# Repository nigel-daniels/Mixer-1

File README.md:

# Mixer

This design is based on the mixer by [Humberto Martínez Barberá](https://www.hackster.io/mb_humberto/eurorack-4-channel-mixer-with-vu-meter-535570). In this design I dropped the peak detection option and added an input channel as I have five VCOs that can generate source signals. I also swapped the electrolytic caps to tantalum as that's what I had on hand.

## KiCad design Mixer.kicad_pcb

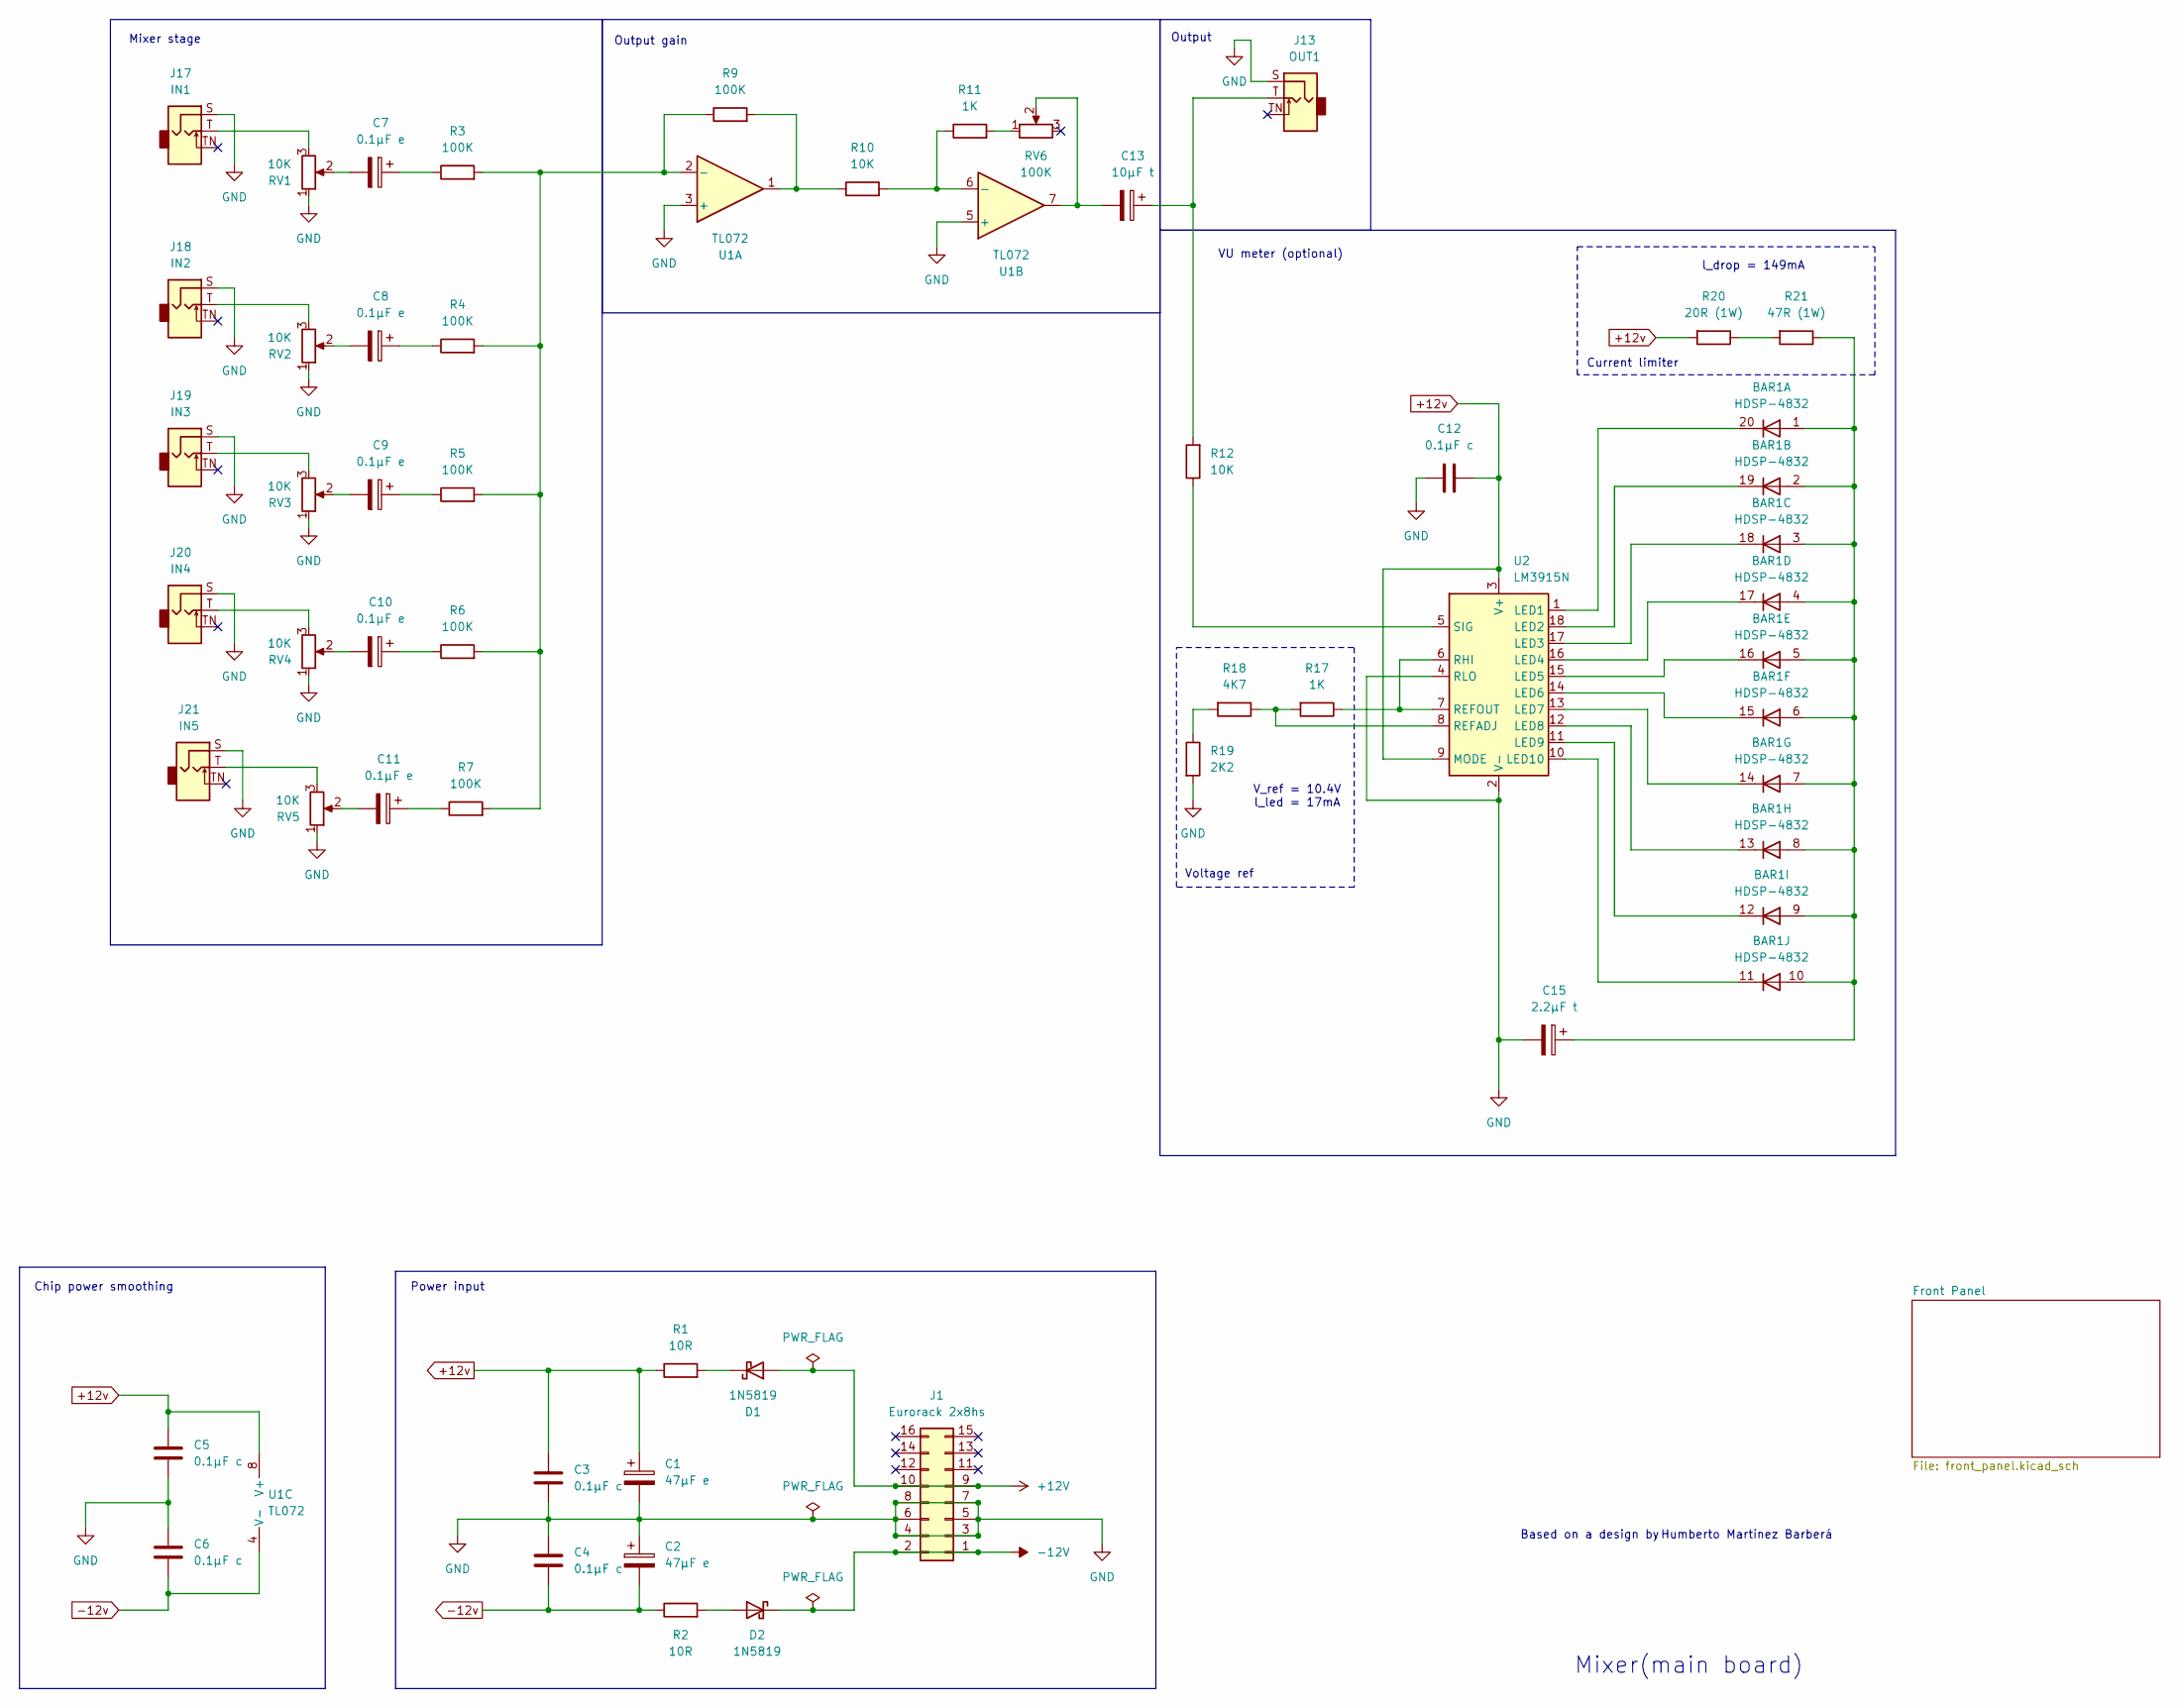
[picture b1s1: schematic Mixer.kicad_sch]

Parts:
BAR1: HDSP-4832
C1, C2: 47μF e; CP_Radial_D5.0mm_P2.50mm
C3, C4, C5, C6, C12: 0.1μF c; C_Disc_D4.7mm_W2.5mm_P5.00mm
C7, C8, C9, C10, C11: 0.1μF e; CP_Radial_D4.0mm_P1.50mm
C13: 10μF t; C_Disc_D4.7mm_W2.5mm_P5.00mm
C15: 2.2μF t; C_Disc_D4.7mm_W2.5mm_P5.00mm
D1, D2: 1N5819; D_DO-41_SOD81_P10.16mm_Horizontal
J1: Eurorack 2x8hs; PinHeader_2x08_P2.54mm_Vertical
J13: OUT1; Jack_3.5mm_QingPu_WQP-PJ398SM_Vertical_CircularHoles
J17: IN1; Jack_3.5mm_QingPu_WQP-PJ398SM_Vertical_CircularHoles
J18: IN2; Jack_3.5mm_QingPu_WQP-PJ398SM_Vertical_CircularHoles
J19: IN3; Jack_3.5mm_QingPu_WQP-PJ398SM_Vertical_CircularHoles
J20: IN4; Jack_3.5mm_QingPu_WQP-PJ398SM_Vertical_CircularHoles
J21: IN5; Jack_3.5mm_QingPu_WQP-PJ398SM_Vertical_CircularHoles
R1, R2: 10R; R_Axial_DIN0204_L3.6mm_D1.6mm_P2.54mm_Vertical
R3, R4, R5, R6, R7: 100K; R_Axial_DIN0204_L3.6mm_D1.6mm_P5.08mm_Horizontal
R9: 100K; R_Axial_DIN0204_L3.6mm_D1.6mm_P2.54mm_Vertical
R10, R12: 10K; R_Axial_DIN0204_L3.6mm_D1.6mm_P5.08mm_Horizontal
R11: 1K; R_Axial_DIN0204_L3.6mm_D1.6mm_P5.08mm_Horizontal
R17: 1K; R_Axial_DIN0204_L3.6mm_D1.6mm_P2.54mm_Vertical
R18: 4K7; R_Axial_DIN0204_L3.6mm_D1.6mm_P2.54mm_Vertical
R19: 2K2; R_Axial_DIN0204_L3.6mm_D1.6mm_P2.54mm_Vertical
R20: 20R (1W); R_Axial_DIN0414_L11.9mm_D4.5mm_P15.24mm_Horizontal
R21: 47R (1W); R_Axial_DIN0617_L17.0mm_D6.0mm_P20.32mm_Horizontal
RV1, RV2, RV3, RV4, RV5: 10K; Potentiometer_Alps_RK09L_Single_Vertical
RV6: 100K; Potentiometer_Alps_RK09L_Single_Vertical
U1: TL072; DIP-8_W7.62mm
U2: LM3915N; DIP-18_W7.62mm

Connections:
+12V: D1.2 (A), J1.9, J1.10
+12v: C1.1, C3.1, C5.1, C12.2, R1.1, R20.2, U1.8 (V+), U2.3 (V+), U2.9 (MODE)
-12V: D2.1 (K), J1.1, J1.2
-12v: C2.2, C4.2, C6.2, R2.1, U1.4 (V-)
GND: C1.2, C2.1, C3.2, C4.1, C5.2, C6.1, C12.1, C15.2, J1.3, J1.4, J1.5, J1.6, J1.7, J1.8, J13.S, J17.S, J18.S, J19.S, J20.S, J21.S, R19.2, RV1.1, RV2.1, RV3.1, RV4.1, RV5.1, U1.3 (+), U1.5 (+), U2.2 (V-), U2.4 (RLO)
unnamed: BAR1.1 (A), BAR1.2 (A), BAR1.3 (A), BAR1.4 (A), BAR1.5 (A), BAR1.6 (A), BAR1.7 (A), BAR1.8 (A), BAR1.9 (A), BAR1.10 (A), C15.1, R21.1
unnamed: BAR1.20 (K), U2.1 (LED1)
unnamed: BAR1.19 (K), U2.18 (LED2)
unnamed: BAR1.18 (K), U2.17 (LED3)
unnamed: BAR1.17 (K), U2.16 (LED4)
unnamed: BAR1.16 (K), U2.15 (LED5)
unnamed: BAR1.15 (K), U2.14 (LED6)
unnamed: BAR1.14 (K), U2.13 (LED7)
unnamed: BAR1.13 (K), U2.12 (LED8)
unnamed: BAR1.12 (K), U2.11 (LED9)
unnamed: BAR1.11 (K), U2.10 (LED10)
unnamed: C7.1, R3.1
unnamed: C7.2, RV1.2
unnamed: C8.1, R4.1
unnamed: C8.2, RV2.2
unnamed: C9.1, R5.1
unnamed: C9.2, RV3.2
unnamed: C10.1, R6.1
unnamed: C10.2, RV4.2
unnamed: C11.1, R7.1
unnamed: C11.2, RV5.2
unnamed: C13.1, J13.T, R12.2
unnamed: C13.2, RV6.2, U1.7
unnamed: D1.1 (K), R1.2
unnamed: D2.2 (A), R2.2
unnamed: J17.T, RV1.3
unnamed: J18.T, RV2.3
unnamed: J19.T, RV3.3
unnamed: J20.T, RV4.3
unnamed: J21.T, RV5.3
unnamed: R9.2, R10.1, U1.1
unnamed: R11.2, RV6.1
unnamed: R18.2, R19.1
unnamed: R20.1, R21.2
unnamed: R3.2, R4.2, R5.2, R6.2, R7.2, R9.1, U1.2 (-)
unnamed: R10.2, R11.1, U1.6 (-)
unnamed: R17.2, R18.1, U2.8 (REFADJ)
unnamed: R17.1, U2.6 (RHI), U2.7 (REFOUT)
unnamed: R12.1, U2.5 (SIG)

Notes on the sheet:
Voltage ref
Mixer stage
Output
Output gain
l_drop = 149mA
Current limiter
Power input
Chip power smoothing
Humberto Martínez Barberá
V_ref = 10.4V l_led = 17mA
Based on a design by
Mixer(main board)
VU meter (optional)

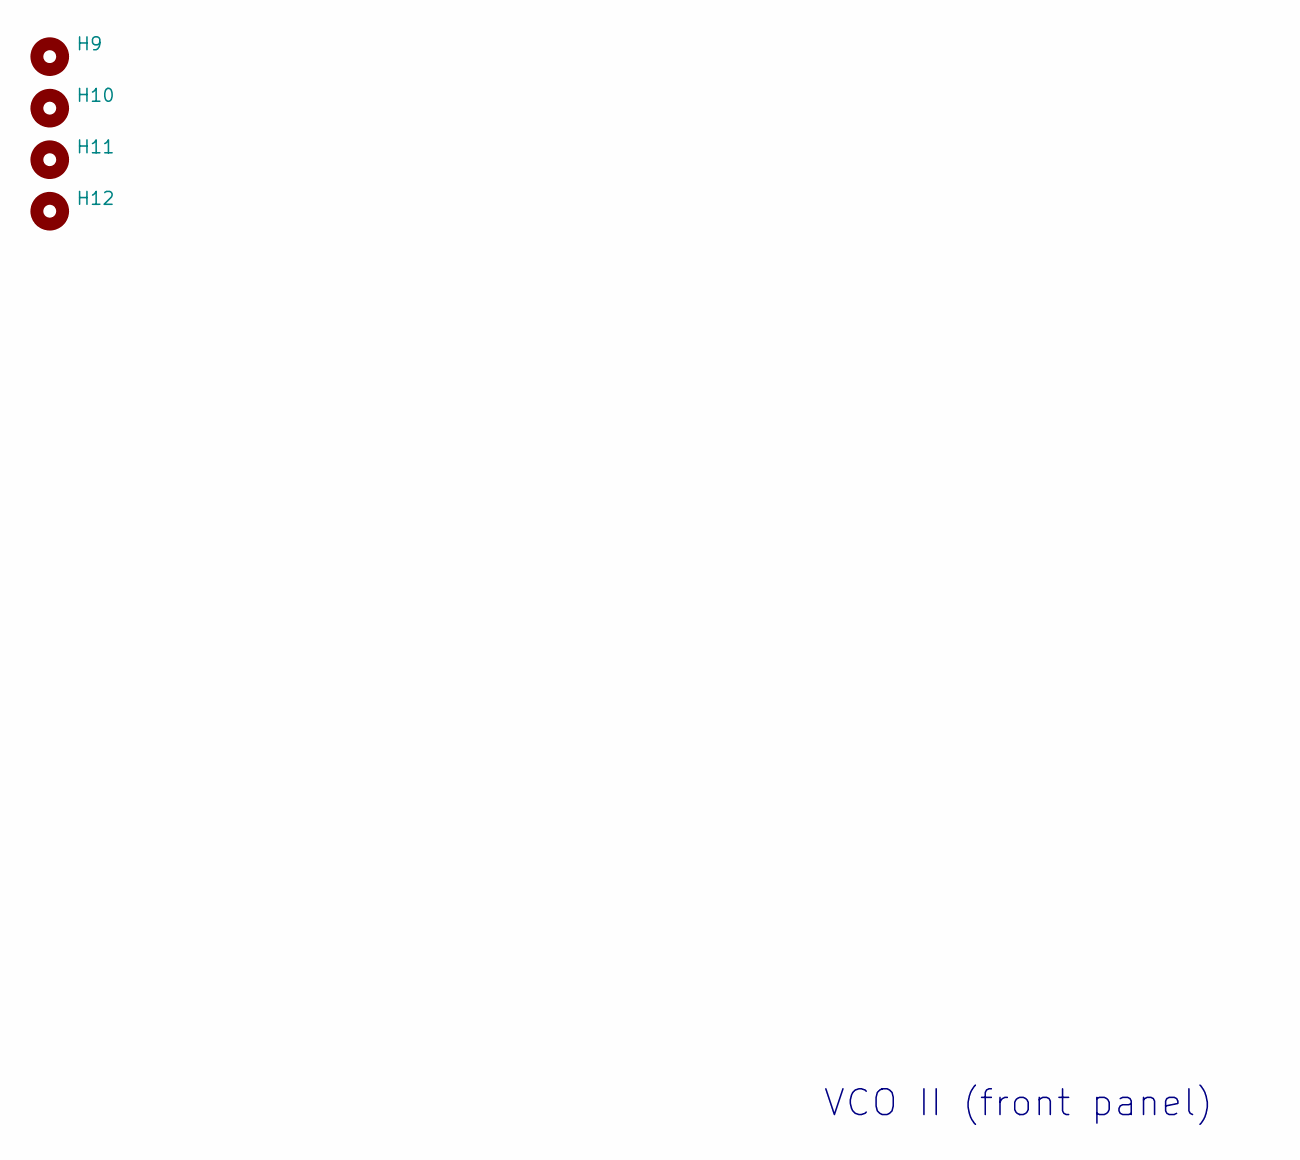
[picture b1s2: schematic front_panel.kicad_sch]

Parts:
H9, H10, H11, H12: MountingHole_3.2mm_M3

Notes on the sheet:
VCO II (front panel)

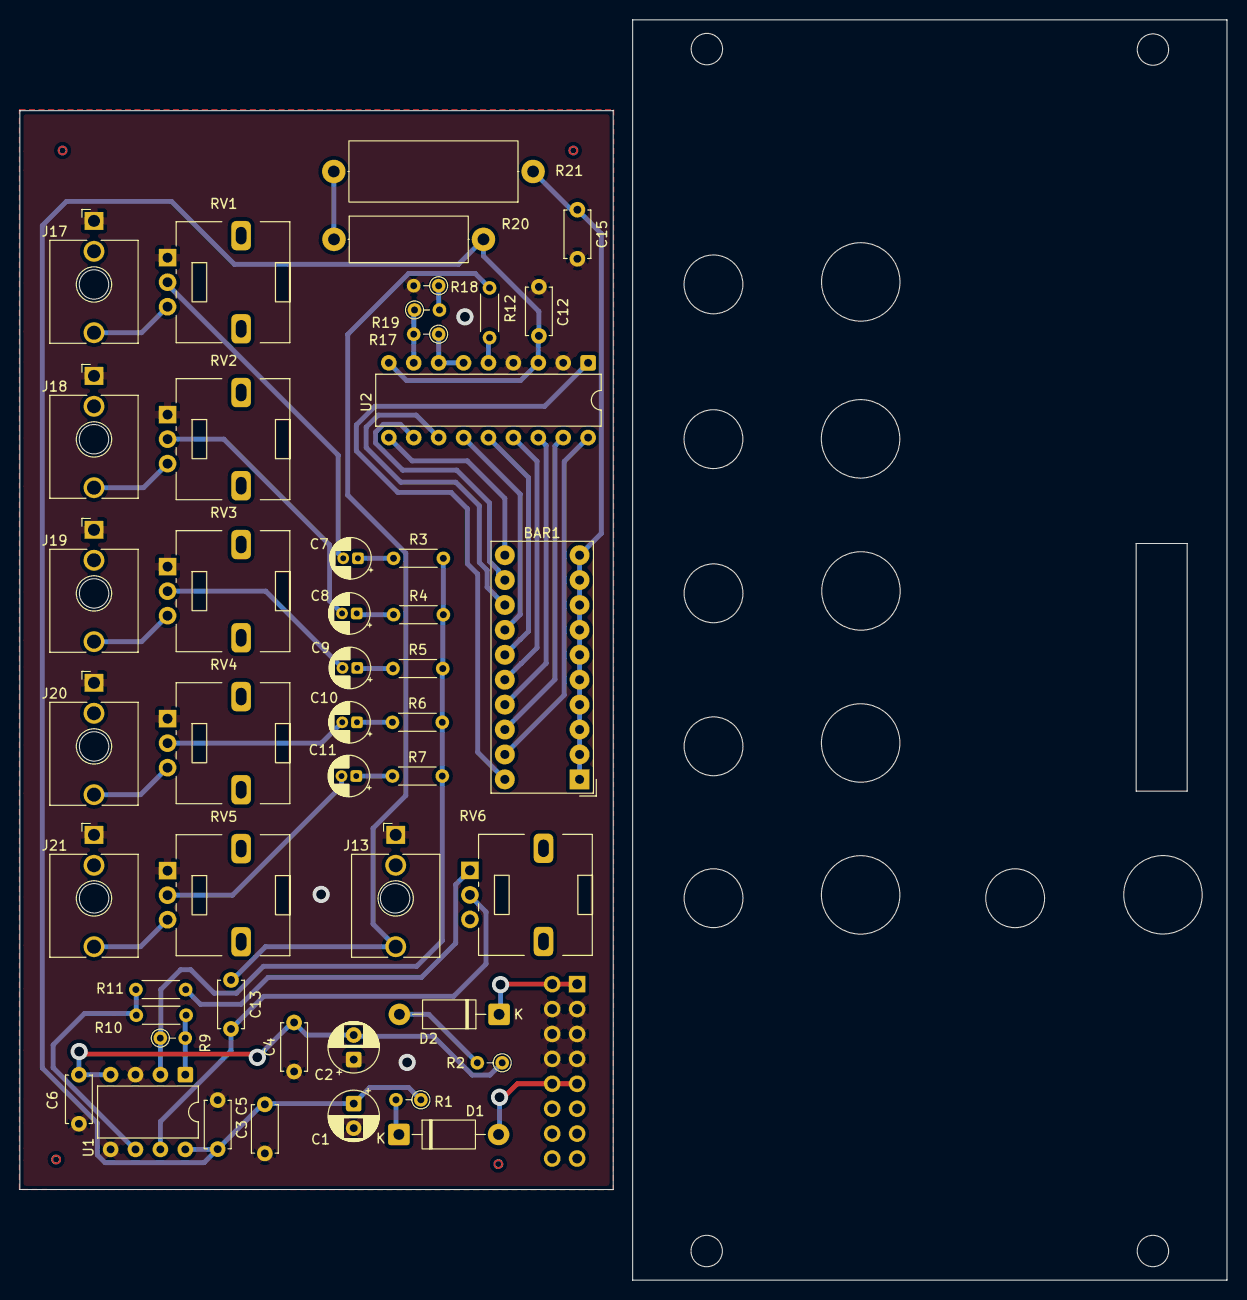
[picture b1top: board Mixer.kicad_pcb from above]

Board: 2 copper layers, 123.1 x 128.5 mm, 52 parts (1 on the bottom side), 44 nets.

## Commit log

2026-04-16 updated ignore
2026-04-16 Ignore update and removed backups
2026-04-16 spaced PCB routing
2026-04-19 Update to reduce FP traces and final self-etch print.
2026-04-24 PCB update
